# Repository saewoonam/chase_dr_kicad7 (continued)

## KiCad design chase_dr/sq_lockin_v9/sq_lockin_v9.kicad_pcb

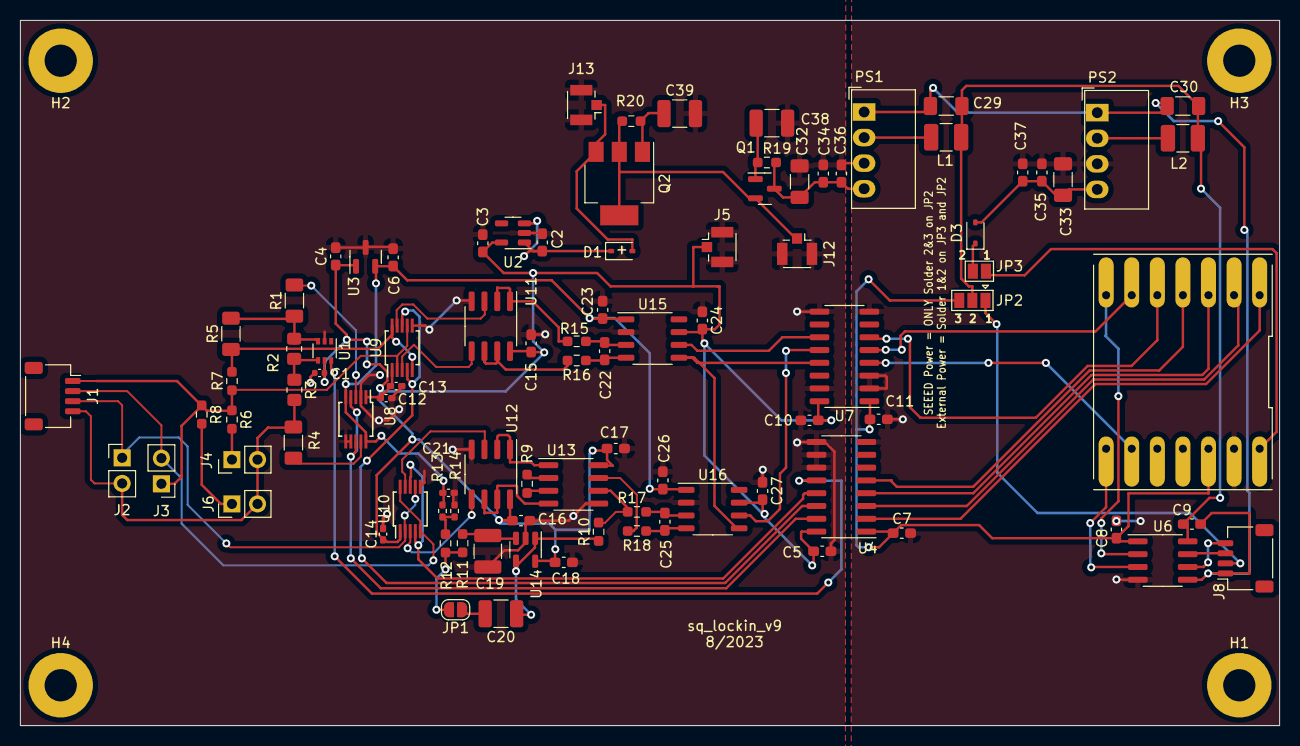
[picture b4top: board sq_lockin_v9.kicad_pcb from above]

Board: 2 copper layers, 125.0 x 70.0 mm, 97 parts (0 on the bottom side), 69 nets.

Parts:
C1: 100nF_0402; C_0402_1005Metric
C2, C3, C4, C6: 1uF; C_0603_1608Metric_Pad1.08x0.95mm_HandSolder
C5, C7, C8, C9, C10, C11, C15, C16, C17, C18, C22, C23, C24, C25, C26, C27, C34, C35: 100nF; C_0603_1608Metric_Pad1.08x0.95mm_HandSolder
C12, C13, C14, C21: 100nF_0402; C_0402_1005Metric_Pad0.74x0.62mm_HandSolder
C19: 10uF; C_1210_3225Metric_Pad1.33x2.70mm_HandSolder
C20, C38, C39: 47uF; C_1210_3225Metric_Pad1.33x2.70mm_HandSolder
C29, C30: 4.7uF_1206_50V; C_1206_3216Metric_Pad1.33x1.80mm_HandSolder
C32, C33: 10uF_1206_50V; C_1206_3216Metric_Pad1.33x1.80mm_HandSolder
C36, C37: 10nF; C_0603_1608Metric_Pad1.08x0.95mm_HandSolder
D1, D3: LBAT54HT1G; D_SOD-323
H1, H2, H3, H4: MountingHole; MountingHole_3.2mm_M3_Pad
J1: Conn_01x04; JST_SH_SM04B-SRSS-TB_1x04-1MP_P1.00mm_Horizontal
J2, J3, J4, J6: Conn_01x02_Male_2.54mm; PinHeader_1x02_P2.54mm_Vertical
J5, J12, J13: Conn_Coaxial; U.FL_Hirose_U.FL-R-SMT-1_Vertical
J8: JST_SH_Conn_01x04_i2c_horizontal; JST_SH_SM04B-SRSS-TB_1x04-1MP_P1.00mm_Horizontal
JP1: Jumper_2_Open; SolderJumper-2_P1.3mm_Open_RoundedPad1.0x1.5mm
JP2: SolderJumper_3_Open; SolderJumper-3_P1.3mm_Open_Pad1.0x1.5mm
JP3: SolderJumper_2_Open; SolderJumper-2_P1.3mm_Open_Pad1.0x1.5mm
L1, L2: 6.8uH; L_1210_3225Metric_Pad1.42x2.65mm_HandSolder
PS1, PS2: B0305S; Converter_DCDC_Murata_MEE1SxxxxSC_THT
Q1: BC847C; SOT-23
Q2: FZT851TA; SOT-223-3_TabPin2
R1, R4, R5: 1M_0.1%; R_1206_3216Metric_Pad1.30x1.75mm_HandSolder
R2: 75K_0.1%; R_0805_2012Metric_Pad1.20x1.40mm_HandSolder
R3: 5K_0.1%; R_0805_2012Metric_Pad1.20x1.40mm_HandSolder
R6: 10K 0.1%; R_0603_1608Metric_Pad0.98x0.95mm_HandSolder
R7: 100K_0.1%; R_0603_1608Metric_Pad0.98x0.95mm_HandSolder
R8: 1K 0.1%; R_0603_1608Metric_Pad0.98x0.95mm_HandSolder
R9: 5.49K; R_0603_1608Metric_Pad0.98x0.95mm_HandSolder
R10: 10; R_0603_1608Metric_Pad0.98x0.95mm_HandSolder
R11, R15, R16, R17, R18: 100; R_0603_1608Metric_Pad0.98x0.95mm_HandSolder
R12: 2K; R_0603_1608Metric_Pad0.98x0.95mm_HandSolder
R13, R14: 1K; R_0402_1005Metric_Pad0.72x0.64mm_HandSolder
R19, R20: 1K; R_0603_1608Metric_Pad0.98x0.95mm_HandSolder
U1: SGM3157; SOT-363_SC-70-6
U2: LP5907MFX-3.3; SOT-23-5
U3: REF3325; SOT-23
U4: pi162U; SOIC-16_3.9x9.9mm_P1.27mm
U5: seeed_rp2040; DIP-XIAO-QTPY
U6: PI121; SOIC-8_3.9x4.9mm_P1.27mm
U7: pi142M31; SOIC-16_3.9x9.9mm_P1.27mm
U8, U9, U10: RS2105XN; MSOP-10_3x3mm_P0.5mm
U11, U12: OPA2376; SOIC-8_3.9x4.9mm_P1.27mm
U13: INA826; SOIC-8_3.9x4.9mm_P1.27mm
U14: OPA388; SOT-23-5
U15, U16: HX710C; SOP-8_3.9x4.9mm_P1.27mm

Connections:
+3.3V: C1.1, C3.1, C4.1, C5.1, C10.1, C12.1, C13.1, C14.1, C15.1, C16.1, C17.2, C18.1, C24.2, C27.2, J5.1 (In), U1.5 (V+), U2.5 (OUT), U3.1 (IN), U4.16 (Vcc2), U7.16 (VCC2), U8.1 (VCC), U9.1 (VCC), U10.1 (VCC), U11.8 (V+), U12.8 (V+), U13.8 (Vs+), U14.5 (V+), U15.7 (DVDD), U16.7 (DVDD)
+5VD: JP3.1 (A), U5.14 (5V)
/Dout_I: U7.11 (IND), U15.6 (DOUT)
/Dout_V: U7.12 (INC), U16.6 (DOUT)
/I+: J1.1, J3.1, R6.1, R7.1, R8.1, U9.2, U9.7
/I-: J1.4, J2.2, J4.2, J6.2, R3.2, R4.2
/MC3.3: C7.1, C8.1, C11.1, JP2.3 (B), U4.1 (Vcc1), U5.12 (3V3), U6.1 (VDD1), U7.1 (VCC1)
/P6: U5.5 (P6), U7.6 (OUTD)
/P7: U5.6 (P7), U7.5 (OUTC)
/Sheet621A3D16/in+: U9.3, U11.5 (+)
/Sheet621A3D16/in-: U9.9, U11.3 (+)
/Sheet624B5D4E/ctrl+: U4.14 (OUTB), U9.4, U9.8
/Sheet624B5D4E/in+: R5.1, R7.2, U9.5, U9.10
/Sheet6275CBF8/in+: U10.3, U12.5 (+)
/Sheet6275CBF8/in-: U10.9, U12.3 (+)
/Sheet62237673/Clk_in: U7.13 (OUTB), U15.5 (PD_SCK), U16.5 (PD_SCK)
/Sheet62237673/V+: R16.2, U11.6 (-), U11.7
/Sheet62237673/V-: R15.2, U11.1, U11.2 (-)
/V+: J1.2, J3.2, U10.5, U10.10
/V-: J1.3, J2.1, U10.2, U10.7
/analog: D1.2 (A), J13.1 (In), Q2.3 (E)
/power/digital: C33.1, C35.2, C37.2, D3.2 (A), PS2.4 (+Vout)
/rx: U5.8 (P1), U6.3 (VOB)
/sheet624D2E57/V+: R18.2, U13.7
/sheet624D2E57/V-: R10.2, R17.2, U13.6 (Ref)
/sheet624D2E58/ctrl+: U4.13 (OUTC), U10.4, U10.8
/sheet6256EE2A/ctrl+: U4.15 (OUTA), U8.4, U8.8
/sheet6256EE2A/out+: R1.2, U8.3
/sheet6256EE2A/out-: R4.1, U8.9
/tx: U5.7 (P0), U6.2 (VIA)
/vref: C6.1, C21.2, C23.1, C26.1, R13.1, U3.2 (OUT), U8.5, U8.10, U15.1 (VREF), U16.1 (VREF)
GND: C1.2, C2.2, C3.2, C4.2, C5.2, C6.2, C10.2, C12.2, C13.2, C14.2, C15.2, C16.2, C17.1, C18.2, C19.2, C21.1, C23.2, C24.1, C26.2, C27.1, C32.2, C34.1, C36.1, C38.2, C39.2, J5.2 (Ext), J12.2 (Ext), J13.2 (Ext), PS1.3 (0V), R14.2, U1.2 (GND), U2.2 (GND), U3.3 (GND), U4.9 (GND2), U4.10 (INF), U4.11 (INE), U7.9 (GND2), U7.15 (GND2), U8.2, U8.6 (GND), U8.7, U9.6 (GND), U10.6 (GND), U11.4 (V-), U12.4 (V-), U13.5 (Vs-), U14.2 (V-), U15.2 (AGND), U16.2 (AGND)
GNDD: C7.2, C8.2, C11.2, C33.2, C35.1, C37.1, PS2.3 (0V), U4.8 (GND1), U5.13 (GND), U6.4 (GND1), U7.2 (GND1), U7.3 (INA), U7.8 (GND1)
GNDPWR: C9.2, C29.2, C30.2, J8.1 (gnd), PS1.1 (-Vin), PS2.1 (-Vin), U6.5 (GND2)
unnamed: C2.1, D1.1 (K), U2.1 (IN), U2.3 (EN)
unnamed: D3.1 (K), JP3.2 (B)
unnamed: J4.1, R6.2
unnamed: J6.1, R8.2
unnamed: J8.4 (SCL), U6.6 (VIB)
unnamed: J8.3 (SDA), U6.7 (VOA)
unnamed: J8.2 (VCC), JP2.1 (A)
unnamed: J12.1 (In), Q1.2 (E), Q2.2 (C), R20.1
unnamed: C20.2, JP1.1 (A)
unnamed: JP1.2 (B), R11.2, R12.1
unnamed: L1.1, PS1.2 (+Vin)
unnamed: C32.1, C34.2, C36.2, PS1.4 (+Vout), Q1.3 (C), R19.1
unnamed: L2.1, PS2.2 (+Vin)
unnamed: C38.1, Q1.1 (B), R19.2
unnamed: C39.1, Q2.1 (B), R20.2
unnamed: R1.1, R2.1, R5.2, U1.3
unnamed: R2.2, R3.1, U1.4
unnamed: R9.1, U13.2 (Rg)
unnamed: R9.2, U13.3 (Rg)
unnamed: R12.2, R13.2, R14.1
unnamed: U4.2 (INA), U5.1 (P26)
unnamed: U4.3 (INB), U5.2 (P27)
unnamed: U4.4 (INC), U5.3 (P28)
unnamed: U4.5 (IND), U5.4 (P29)
unnamed: U1.6, U4.12 (OUTD)
unnamed: U5.9 (P2), U7.4 (INB)
unnamed: U12.1, U12.2 (-), U13.1 (-)
unnamed: U12.6 (-), U12.7, U13.4 (+)
unnamed: C19.1, R11.1, U14.3 (+)
unnamed: C20.1, R10.1, U14.1, U14.4 (-)
unnamed: C22.2, R15.1, U15.3 (INN)
unnamed: C22.1, R16.1, U15.4 (INP)
unnamed: C25.2, R17.1, U16.3 (INN)
unnamed: C25.1, R18.1, U16.4 (INP)
VD: C9.1, C29.1, C30.1, JP2.2 (C), L1.2, L2.2, U6.8 (VDD2)

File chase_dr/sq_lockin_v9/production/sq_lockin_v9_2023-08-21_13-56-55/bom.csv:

Designator,Footprint,Quantity,Value,LCSC Part #
"C1, C12, C13, C14",0402,4,100nF_0402,C1525
"C10, C11, C15, C16, C17, C18, C22, C23, C24, C25, C26, C27, C34, C35, C5, C7, C8, C9",0603,18,100nF,C14663
C19,1210,1,10uF,C318781
"C2, C3, C4, C6",0603,4,1uF,C15849
C20,1210,1,47uF,C396816
C21,0402,1,100nF_0402,C14663
"C29, C30",1206,2,4.7uF_1206_50V,C29823
"C32, C33",1206,2,10uF_1206_50V,C13585
"C36, C37",0603,2,10nF,C57112
"C38, C39",1210,2,47uF,C84494
"D1, D3",D_SOD-323,2,LBAT54HT1G,C12744
J1,JST_SH_SM04B-SRSS-TB_1x04-1MP_P1.00mm_Horizontal,1,Conn_01x04,C371571
"J12, J13, J5",U.FL_Hirose_U.FL-R-SMT-1_Vertical,3,Conn_Coaxial,C88373
"J2, J3, J4, J6",PinHeader_1x02_P2.54mm_Vertical,4,Conn_01x02_Male_2.54mm,C358684
J8,JST_SH_SM04B-SRSS-TB_1x04-1MP_P1.00mm_Horizontal,1,JST_SH_Conn_01x04_i2c_horizontal,C371571
"L1, L2",1210,2,6.8uH,C87558
"PS1, PS2",Converter_DCDC_Murata_MEE1SxxxxSC_THT,2,B0305S,C909802
Q1,SOT-23,1,BC847C,C8664
Q2,SOT-223-3_TabPin2,1,FZT851TA,C87950
"R1, R4, R5",1206,3,1M_0.1%,C2984499
R10,0603,1,10,C22859
"R11, R15, R16, R17, R18",0603,5,100,C22775
R12,0603,1,2K,C22975
"R13, R14",0402,2,1K,C25804
"R19, R20",0603,2,1K,C21190
R2,0805,1,75K_0.1%,C111588
R3,0805,1,5K_0.1%,C2828700
R6,0603,1,10K 0.1%,C723396
R7,0603,1,100K_0.1%,C122538
R8,0603,1,1K 0.1%,C328422
R9,0603,1,5.49K,C23069
U1,SOT-363_SC-70-6,1,SGM3157,C394901
"U10, U8, U9",MSOP-10_3x3mm_P0.5mm,3,RS2105XN,C237025
"U11, U12",SOIC-8_3.9x4.9mm_P1.27mm,2,OPA2388,C46316
U13,SOIC-8_3.9x4.9mm_P1.27mm,1,INA826,C38433
U14,SOT-23-5,1,OPA388,C30878
"U15, U16",SOP-8_3.9x4.9mm_P1.27mm,2,HX710C,C124156
U2,SOT-23-5,1,LP5907MFX-3.3,C80670
U3,SOT-23,1,REF3325,C69039
U4,SOIC-16_3.9x9.9mm_P1.27mm,1,pi162U,C471609
U6,SOIC-8_3.9x4.9mm_P1.27mm,1,PI121,C471589
U7,SOIC-16_3.9x9.9mm_P1.27mm,1,pi142M31,C471606

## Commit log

2023-08-21 Initial commit for square_lockin_v9 with kicad7
2023-08-24 Add uart mux v3 individual power for each uart with enable
2023-08-24 Add transimpedance design
2023-08-25 Add pdf notes to transimpedance amp folder
2023-08-28 Add usb_pd tweak usb_pd to add capacitance multiplier filters before vregulation
2023-08-28 add gitignore
